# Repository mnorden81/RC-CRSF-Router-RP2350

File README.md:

# RC-CRSF-Router-RP2350 („CRSF-Router 8“)

CRSF-Verteiler für ELRS-Empfänger auf einem **Waveshare RP2350-Zero**. Der große Bruder des [RC-CRSF-Router-ESP32-S3](https://github.com/mnorden81/RC-CRSF-Router-ESP32-S3): gleiche Weiterleitungsregeln, gleiche Bedienung über das Lua-Menü, aber bis zu 7 statt 2 Ports und **kein WLAN**.

Zwei Versionen, ein Sketch (Auswahl oben in `pins.h`):

| Version | Ports | Pins am RP2350-Zero | Im Sender | Platine |
|---|---|---|---|---|
| **Router** | Eingang + 7 Ports | alle, auch die 5 Pads an der Unterkante | `CRSF-Router8@15` | [hardware/Router](hardware/Router/) |
| **Test** | Eingang + 6 Ports | nur die beiden seitlichen Stiftleisten | `CRSF-Router8 Test@15` | keine, nur für das Steckbrett |

> Stand: Firmware **v0.4.1** („Version 2“: Filter, Telemetrie-Bremse, Geräteliste; dazu gezielte Zustellung und Lua-Vorrang nach ELRS-Vorbild), kompiliert und mit Host-Tests geprüft, **noch nicht auf Hardware getestet**. Erster Hardwaretest am 05.11.2026 auf dem Steckbrett (v0.2.0, nur seitliche Stiftleisten): der Sender findet den Router als „CRSF-Router8@14“ neben dem S3-Router und zwei Sound-Minis. Die Router-Platine ist seit 11.11.2026 fertig geroutet (DRC ohne Fehler), aber noch nicht bestellt.

| Testaufbau | RP2350-Zero auf dem Steckbrett |
|---|---|
|  |  |

## Was er macht

Der Router hängt an einem freien CRSF-Port des Empfängers und verteilt CRSF auf bis zu 7 Geräte (Test-Version: 6): Multiswitche (auch die Ziege-One-Module), Soundmodule, Sensoren oder weitere Router.

- Vom Empfänger nach unten geht alles, außer Anfragen an die eigene Adresse. Anfragen an ein Gerät, dessen Port der Router schon kennt, gehen nur an diesen Port (ab v0.4.1).
- Von unten nach oben geht alles (Telemetrie, Lua-Antworten, DEVICE_INFO).
- Zwischen den Ports geht nichts, so entstehen keine Schleifen.
- Weitergegeben werden nur vollständige Frames mit gültiger CRC, unverändert.
- Jeder Port hat eine eigene Warteschlange und sendet nicht blockierend. Ein langsamer Port bremst die anderen nicht aus. Wird es eng, fällt zuerst ein alter RC-Frame weg, dann Telemetrie, Lua-Antworten zuletzt.

### Neu in v0.4.0 („Version 2“)

Die Ideen stammen aus dem Vergleich mit dem CRSF-Switch von Wilhelm Meier (wmucpp). Ohne Änderung im Lua-Menü verhält sich der Router genau wie v0.3.0.

| Funktion | Was sie macht | Wirkt |
|---|---|---|
| **Filter je Port** | RC-Kanäle (0x16/0x17) und LinkStats (0x14/0x1C/0x1D) nach unten je Port an oder aus. Ping, Lua und Schaltbefehle gehen immer durch. | sofort |
| **Telemetrie-Bremse je Port** | Telemetrie von unten nach oben: alle, höchstens 50/20/10/5/2/1 Frames pro Sekunde **je Sensor-Art**, oder aus. Bei RPM, Temperatur und Zellen zählt jede Quelle einzeln. DEVICE_INFO und Lua-Antworten gehen immer hoch. | sofort |
| **Geräteliste** | Der Router fragt 2 s und 6 s nach dem Start alle Ports per Ping ab und merkt sich die Antworten (bis 4 Geräte je Port, auch hinter einem weiteren Router). Lua-Ordner „Geräte“ zeigt sie, „Geräte suchen“ fragt neu ab. Antworten auf den eigenen Ping bleiben im Router. Die USB-Konsole listet jede Änderung. | sofort |

### Neu in v0.4.1 (Ideen aus dem ELRS-Empfänger)

Der ELRS-Empfänger hat seit Version 4.0 selbst einen kleinen CRSF-Router (Funkstrecke, CRSF-Port und auf ESP32-Empfängern ein zweiter UART). Drei seiner Regeln hat der Router übernommen. Im Lua-Menü ändert sich nichts, die Einstellungen bleiben erhalten.

| Funktion | Was sie macht |
|---|---|
| **Adress-Lernen + gezielte Zustellung** | Der Router merkt sich, hinter welchem Port welche Adresse sitzt (aus jedem Lua-, Ping- oder Befehls-Frame von unten und aus Heartbeats 0x0B). Lua-Anfragen und Schaltbefehle an ein bekanntes Gerät gehen nur noch an diesen Port. Unbekannte Ziele, Broadcasts (0x00) und 0xC8 gehen weiter an alle. Steckt man ein Gerät um, gilt der Port, von dem es sich zuletzt gemeldet hat. „Geräte suchen“ vergisst alle gelernten Adressen. |
| **Überschreiben statt Verwerfen** | Wartet noch ein Telemetrie-Frame gleicher Art (bei RPM/Temperatur/Zellen gleicher Quelle) vom selben Port, ersetzt der neue ihn an seinem Platz. So geht immer der neueste Wert hoch, die Schlange läuft nicht voll. |
| **Lua-Vorrang nach oben** | Ping-Antworten und Lua-Frames (0x28–0x2D) überholen wartende Telemetrie. Das Lua-Menü bleibt flüssig, auch wenn viele Module Telemetrie schicken. |

Die USB-Konsole zeigt dazu „gezielt“ und „ersetzt“ in der Statuszeile.

Zum Merken: Schaltet man an einem Port die RC-Kanäle ab, sieht ein Gerät dort (auch ein weiterer Router) kein RC-Signal mehr und geht in Failsafe.

## Status-LED (RGB-LED auf dem Board)

| LED | Bedeutung |
|---|---|
| grün langsam | RC-Signal in Ordnung |
| rot schnell | kein RC-Signal / Failsafe |
| gelb Doppelblitz | Adresskonflikt oder ein Port ließ sich nicht starten |

Sind Rot und Grün vertauscht, im Lua-Menü „LED Farbfolge“ auf **RGB** stellen.

## Lua-Menü (ELRS Lua / TBS Agent)

Ab v0.4.0 werden die Feld-IDs fortlaufend vergeben, sie haben sich gegenüber v0.3.0 verschoben (nur wichtig für eigene Skripte). Die Einstellungen aus v0.3.0 übernimmt der Router beim ersten Start.

| Eintrag | Werte |
|---|---|
| Version | z. B. „0.4.1 Router“ |
| Ordner **Ports (nach Neustart)** | |
| ↳ Port 1 … Port 7 | Aus, 57600, 115200, 400000, **420000**, 921600 |
| Ordner **Filter** → je Port ein Ordner | |
| ↳ RC-Kanaele runter | Aus, **Ein** |
| ↳ LinkStats runter | Aus, **Ein** |
| ↳ Telemetrie hoch | **Alle**, 50/s, 20/s, 10/s, 5/s, 2/s, 1/s, Aus |
| Ordner **Geraete** | |
| ↳ Geraete suchen | Nein, Jetzt |
| ↳ Port 1 … Port 7 | Anzeige, z. B. „Multiswitch@3, Sound@2“, „kein Geraet“, „aus“ |
| Modul Adresse | 0–15, Vorgabe **15** |
| Ordner **Telemetrie** | |
| ↳ Spannung senden | **Aus**, als RxBt, als Zellen |
| ↳ Spannung Korrektur | −0,5 … +0,5 V |
| ↳ Spannung | Anzeige |
| ↳ Temperatur senden | **Aus**, Ein |
| ↳ Chiptemperatur | Anzeige |
| Ordner **Status** | |
| ↳ Frames runter / hoch / Verworfen / Gefiltert / CRC-Fehler unten | Zähler |
| ↳ Adresskonflikt | ja/nein |
| ↳ Ports aktiv | je Port: Nummer = Gerät antwortet, `.` still, `-` aus, `!` Fehler |
| LED Farbfolge | **GRB**, RGB |
| Neustart | Nein, Jetzt |
| Geraetename | „CRSF-Router8“ bzw. „CRSF-Router8 Test“ |

Router: 65 Felder, Test: 59 Felder (Port 7 fehlt überall). Im Sender erscheint der Router als **CRSF-Router8@15** bzw. **CRSF-Router8 Test@15** (Name@Adresse).

## Brauche ich den Router überhaupt? (ELRS 4.x)

Ab ELRS 4.0 haben **ESP32-Empfänger** einen zweiten seriellen Port („Serial 2“, im ELRS-Lua oder WebUI auf „CRSF“ stellen; bei PWM-Empfängern lassen sich dafür PWM-Pins umstellen). Der Empfänger verteilt CRSF dann selbst zwischen beiden Ports.

- **Bis zu 2 Module** an einem ESP32-Empfänger: kein Router nötig.
- **Mehr als 2 Module**, **ESP8285-Empfänger** (nur ein CRSF-Port, z. B. EP1/EP2, RP1–RP3) oder Bedarf an Filtern, Telemetrie-Bremse und Geräteliste: Router verwenden.
- Mit Serial 2 kann der Router auch dort hängen, dann bleibt der erste Port für ein anderes Gerät frei.

## Mehrere Router

Jeder Router hat eine eigene WM-Adresse (0–15 → CRSF 0xC0 + Adresse). Mehrere Router im Modell (auch gemischt mit dem S3-Router) bekommen verschiedene Adressen, z. B. 15, 14, 13. Meldet ein Gerät weiter hinten dieselbe Adresse, blinkt die LED gelb. Router lassen sich verketten; mehr als 3 Router hintereinander sind nicht sinnvoll (je ca. 0,6 ms Verzögerung).

## Anschlüsse (Kurzfassung)

| Port | Router TX | Router RX | Test TX | Test RX | Art |
|---|---|---|---|---|---|
| Uplink (Empfänger) | GP0 | GP1 | GP0 | GP1 | Hardware-UART, fest 420000 Baud |
| Port 1 | GP2 | GP3 | GP2 | GP3 | PIO-UART |
| Port 2 | GP4 | GP5 | GP4 | GP5 | Hardware-UART |
| Port 3 | GP6 | GP7 | GP6 | GP7 | PIO-UART |
| Port 4 | GP8 | GP9 | GP8 | GP14 | PIO-UART |
| Port 5 | GP10 | GP11 | GP15 | GP27 | PIO-UART |
| Port 6 | GP12 | GP13 | GP28 | GP29 | PIO-UART |
| Port 7 | GP14 | GP15 | – | – | PIO-UART |
| Spannung | GP26 | | GP26 | | nur mit externem Teiler 33k/10k, auf der Platine nicht vorhanden |

Lage am Board (Oberseite, USB oben): rechte Leiste GP0–GP8, untere Kante GP9–GP13 (nur Lötpads), linke Leiste 5V, GND, 3V3, GP29, GP28, GP27, GP26, GP15, GP14. Die **Router**-Version braucht die Pads unten (5er-Stiftleiste einlöten), die **Test**-Version kommt mit den beiden seitlichen Leisten aus. Mehr als 8 UARTs (2 Hardware + 6 PIO) schafft der RP2350 nicht, deshalb sind 7 Ports das Maximum.

TX des Routers an RX des Geräts und umgekehrt, GND gemeinsam. Details und Schaltplan: [hardware/README.md](hardware/README.md).

## Firmware flashen

Der RP2350 hat kein WLAN, Updates gehen immer über USB. Am einfachsten ist Weg 1, dafür braucht man keine Software.

### Weg 1: Fertige Datei aus GitHub (ohne Arduino IDE)

1. Auf GitHub angemeldet sein (sonst gibt es keinen Download-Knopf).
2. In diesem Repo oben auf **Actions** klicken, links den Workflow **Firmware bauen** wählen.
3. Den obersten Lauf mit grünem Haken öffnen (Branch `main`).
4. Ganz unten unter **Artifacts** **crsf-router8-rp2350-Router** herunterladen (für das Steckbrett: **crsf-router8-rp2350-Test**) und die ZIP-Datei entpacken. Darin liegt `CRSF-Router8_Router.uf2` bzw. `CRSF-Router8_Test.uf2`.
   Steht dort nichts (Artefakte werden nach 90 Tagen gelöscht): rechts oben **Run workflow** → **Run workflow** klicken, nach ca. 3 Minuten ist ein neuer Lauf fertig.
5. Am RP2350-Zero die Taste **BOOT** gedrückt halten und dabei das USB-C-**Datenkabel** einstecken, dann loslassen.
6. Am PC erscheint ein neues Laufwerk **RP2350** (wie ein USB-Stick).
7. Die `.uf2`-Datei mit der Maus auf dieses Laufwerk ziehen. Das Laufwerk verschwindet, der Router startet von selbst neu. Fertig.

### Weg 2: Arduino IDE

**Einmalig einrichten**

1. Arduino IDE 2.x installieren (https://www.arduino.cc/en/software).
2. **Datei → Einstellungen → Zusätzliche Boardverwalter-URLs**:
   `https://github.com/earlephilhower/arduino-pico/releases/download/global/package_rp2040_index.json`
3. **Werkzeuge → Board → Boardverwalter**: „pico“ suchen, **Raspberry Pi Pico/RP2040/RP2350** (von Earle F. Philhower) in Version **6.3.2** installieren.
4. Weitere Bibliotheken sind nicht nötig.

**Flashen**

1. Repo herunterladen: oben auf GitHub **Code → Download ZIP**, entpacken (oder den vorhandenen Ordner nehmen).
2. **Datei → Öffnen** und `firmware/RC_CRSF_Router_RP2350/RC_CRSF_Router_RP2350.ino` wählen.
3. Version wählen: oben in `pins.h` steht `#define VARIANTE_ROUTER` (Vorgabe, für die Platine). Für die Test-Version (Steckbrett) diese Zeile mit `//` auskommentieren und bei `//#define VARIANTE_TEST` die `//` entfernen.
4. **Werkzeuge → Board → Raspberry Pi Pico/RP2040/RP2350 → Waveshare RP2350 Zero** wählen. Die übrigen Einstellungen unter Werkzeuge bleiben auf Standard.
5. Beim **allerersten Mal**: BOOT-Taste gedrückt halten, USB einstecken, loslassen. Unter **Werkzeuge → Port** „UF2 Board“ wählen.
   Ab dem zweiten Mal: einfach einstecken und unter **Werkzeuge → Port** den COM-Port wählen.
6. Auf den Pfeil **Hochladen** klicken. Der Router startet danach von selbst neu.

**Wenn das Hochladen nicht klappt** (kein Port oder „No drive to deploy“): USB abziehen, BOOT gedrückt halten, wieder einstecken und mit Port „UF2 Board“ erneut hochladen.

Der serielle Monitor (115200) zeigt alle 10 s eine Statuszeile.

## Aufbau des Repos

| Ordner | Inhalt |
|---|---|
| `firmware/RC_CRSF_Router_RP2350/` | Arduino-Sketch (siehe [firmware/README.md](firmware/README.md)) |
| `tests/` | Host-Tests des Routers (`sh tests/run_tests.sh`) |
| `hardware/Router/` | KiCad-Projekt der Router-Platine (geroutet, DRC ohne Fehler), nur THT-Bauteile, plus 3D-Modell `hardware/3d-modell.html` (siehe [hardware/README.md](hardware/README.md)) |
| `hardware/gehaeuse/` | 3D-Druck-Gehäuse (STL/STEP, CadQuery-Quelle, 3D-Vorschau), siehe [hardware/gehaeuse/README.md](hardware/gehaeuse/README.md) |
| `docs/` | Projektbeschreibung (DOCX), Fotos unter `docs/bilder/` |

## Herkunft

Die CRSF-Bibliothek stammt aus RC_Common (CRSF_ESP32 1.1.0), Basis ist [CRSF_ESP32 von Ziege-One](https://github.com/Ziege-One/CRSF_ESP32) (GPL-3.0).

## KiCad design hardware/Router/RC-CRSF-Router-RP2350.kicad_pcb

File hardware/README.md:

# Hardware CRSF-Router 8

Basis ist ein **Waveshare RP2350-Zero** (ca. 23,5 × 18 mm, USB-C, RGB-LED an GP16, BOOT- und RESET-Taste), gesteckt auf eine Verteilerplatine. Jeder Teilnehmer bekommt ein 4-poliges Kabel mit GND, +V und den beiden Signalen, wie bei einem Servoverteiler.

Es gibt **eine** Platine für den Router (Ordner [`Router/`](Router/)): Eingang + 7 Ports, alle Bauteile bedrahtet (THT), 38,4 × 25,5 mm, 2 Lagen. Sie nutzt alle Pins am RP2350-Zero, also beide seitlichen Leisten **und** die 5 Pads unten (GP9–GP13). Firmware-Version `VARIANTE_ROUTER` in `firmware/RC_CRSF_Router_RP2350/pins.h` (Vorgabe).

Die Firmware-Version **Test** (`VARIANTE_TEST`, Eingang + 6 Ports, nur die seitlichen Leisten) ist nur für den Aufbau auf dem Steckbrett gedacht. Für sie gibt es keine Platine.

> Stand 11.11.2026 (abends): **Platine fertig geroutet** (von Martin in KiCad 9, beide Lagen: 144 Leiterbahn-Stücke, 6 Vias, keine Kupferflächen). DRC: 0 Fehler, 0 offene Verbindungen. ERC: 0 Fehler, nur 19 Warnungen „Symbol stimmt nicht mit Bibliothek überein“ bei den Power-Symbolen (harmlos, verschwindet mit „Symbole aus Bibliothek aktualisieren“). Vor der Bestellung noch prüfen: Footprint des RP2350-Zero am echten Board, Abmessungen von F1 im Datenblatt, und die Beschriftung auf der Unterseite (sie liegt teilweise auf Pads, der Hersteller schneidet sie dort weg). Mehr als 8 UARTs schafft der RP2350 nicht (2 Hardware-UARTs + 6 PIO-UARTs), deshalb sind 7 Ports das Maximum.

| Oberseite | Unterseite |
|---|---|
|  |  |

Leiterbahnen beider Lagen (rot oben, blau unten):

3D-Modell (vereinfachte Bauteilkörper, Maße aus der Platine): [`3d-modell.html`](3d-modell.html) herunterladen und im Browser öffnen (braucht Internet für die 3D-Bibliothek).

**Gehäuse für den 3D-Druck:** Unterteil und Deckel zum Aufklipsen, Steckerfeld oben und rechts offen, siehe [`gehaeuse/`](gehaeuse/).

## Aufbau so kompakt wie möglich (11.11.2026)

- Platine 38,4 × 25,5 mm: links der RP2350-Zero (USB-C ragt etwas über die Kante), darunter in einer Reihe parallel zum Zero C1, D1 (liegend) und F1, rechts die Steckerleiste.
- Keine Befestigungslöcher. Befestigung z. B. mit doppelseitigem Klebeband oder Schrumpfschlauch.
- Beschriftung (Name, T/R/V/G-Erklärung, Hinweis „kein HV-BEC“) auf der Unterseite. Oben nur T R V G und die Reihen U, 1–7.
- Steckerleiste in der Reihenfolge **T R V G** (Signale zum RP2350 hin, GND außen), damit TX/RX auf kurzem Weg zum Zero laufen. Signale 0,2 mm, Abstand 0,2 mm: zwischen zwei Pads der Leiste passt eine Leiterbahn.

## Versorgung

- **Nur vom Empfänger:** Die 5–6 V kommen über die Reihe U (Pin V) vom Empfänger-BEC. Es gibt keinen eigenen BEC-Eingang. **Kein HV-BEC (7,4/8,4 V) am Empfänger!**
- **Kein Spannungsregler:** Der RP2350-Zero bekommt VBUS über D1 (1N5819, ca. 0,3 V Verlust) an seinen 5-V-Pin. D1 verhindert, dass USB den Empfänger und die Ports speist.
- **Eine gemeinsame Sicherung** F1 (PTC 3 A) für alle Ports. Bei einem Kurzschluss an einem Port läuft der Empfänger weiter. Nach Beseitigung des Fehlers schaltet sie selbst wieder ein.
- C1 (100 µF) puffert kurze Stromspitzen der Module. Ohne ihn läuft der Router auch.
- Hat ein Modul eine eigene Versorgung, bekommt es einfach kein V-Kabel, damit zwei Netzteile nicht gegeneinander arbeiten.
- Große Verbraucher (Lasten der Multiswitche, Lautsprecher-Verstärker) nicht über diese Platine versorgen.
- **Keine Spannungsmessung:** GP26 bleibt frei, in Lua „Spannung senden“ aus lassen.

## Stückliste

| Ref | Anzahl | Wert | Bauform | Hinweis |
|---|---|---|---|---|
| U1 | 1 | Waveshare RP2350-Zero | direkt aufgelötet | Randkontakte auf die Pads gelötet, ohne Buchsenleisten |
| D1 | 1 | 1N5819 | DO-41, liegend (RM 7,62) | VBUS zum 5-V-Pin, kein Rückstrom bei USB |
| F1 | 1 | PTC 3 A / 16 V, Bourns MF-RG300 | radial, stehend | gemeinsame Sicherung aller Ports |
| C1 | 1 | 100 µF / 10 V | Elko radial Ø 5 mm, RM 2 | puffert Stromspitzen, kann zur Not entfallen |
| J1–J8 | 8 | Stiftleiste 1×4 | 2,54 mm, gerade | Uplink + Port 1–7 |

## KiCad-Projekte

Der Ordner `Router/` enthält ein vollständiges Projekt:

| Datei | Inhalt |
|---|---|
| `RC-CRSF-Router-RP2350.kicad_pro/.kicad_sch/.kicad_pcb` | Projekt, Schaltplan, Platine |
| `RC-CRSF-Router-RP2350_Schaltplan.pdf` | Schaltplan als PDF |
| `Router8.kicad_sym`, `footprints.pretty/` | Projektbibliothek: Symbol und Footprint RP2350-Zero, Stiftleiste 1×4 für die Schiene |
| `sym-lib-table`, `fp-lib-table` | binden die Projektbibliothek ein |
| `vorschau-platine.png`, `vorschau-unterseite.png` | 3D-Ansicht der gerouteten Platine von oben und unten (KiCad-Rendering) |
| `vorschau-routing.png` | Leiterbahnen beider Lagen |

Gespeichert mit KiCad 9.0. Leiterbahnen für TX/RX 0,2 mm (bei 420 kBaud und wenigen mA völlig ausreichend), Netzklasse **Power** (GND, VBUS, +5V, +V der Ports) 0,5 mm mit Via 0,9/0,5 mm, sonst Via 0,6/0,3 mm, Abstand überall 0,2 mm. Das kann jeder übliche Platinenhersteller.

**Nächster Schritt:** Gerber- und Bohrdaten für den Hersteller exportieren (KiCad: Datei → Fertigungsdateien). Sie liegen noch nicht im Repo.

**RP2350-Zero direkt aufgelötet:** Das Board liegt flach auf der Platine, seine Randkontakte werden auf die Pads gelötet (alternativ kurze Stiftleisten durch beide Platinen). Dabei auch die 5 Pads an der Unterkante (GP9–GP13) verlöten. Vor dem Auflöten die Firmware einmal per USB aufspielen und testen.

## Steckerleiste (2,54 mm, gerade)

| Reihe | Bedeutung |
|---|---|
| U (J1) | Uplink zum Empfänger, von hier kommt die Versorgung |
| 1–7 (J2–J8) | Port 1–7, +V über die Sicherung F1 |

Spalten von links: **T** = Router empfängt, vom TX des Geräts, **R** = Router sendet, an RX des Geräts, **V** = +5–6 V, **G** = GND (eckiges Pad, rechts außen). Damit wird jedes Kabel gerade gesteckt.

## Pinbelegung RP2350-Zero

Die Spalten „Test“ gelten nur für den Steckbrett-Aufbau ohne Platine.

| Port | Router TX | Router RX | Test TX | Test RX |
|---|---|---|---|---|
| Uplink (Hardware-UART0) | GP0 | GP1 | GP0 | GP1 |
| Port 1 (PIO) | GP2 | GP3 | GP2 | GP3 |
| Port 2 (Hardware-UART1) | GP4 | GP5 | GP4 | GP5 |
| Port 3 (PIO) | GP6 | GP7 | GP6 | GP7 |
| Port 4 (PIO) | GP8 | GP9 | GP8 | GP14 |
| Port 5 (PIO) | GP10 | GP11 | GP15 | GP27 |
| Port 6 (PIO) | GP12 | GP13 | GP28 | GP29 |
| Port 7 (PIO) | GP14 | GP15 | – | – |
| frei | GP26–GP29 | | GP26, GP9–GP13 (Pads) | |

Lage am Board (Oberseite, USB oben): rechte Leiste GP0–GP8, untere Kante GP9–GP13 (nur Pads), linke Leiste 5V, GND, 3V3, GP29, GP28, GP27, GP26, GP15, GP14.

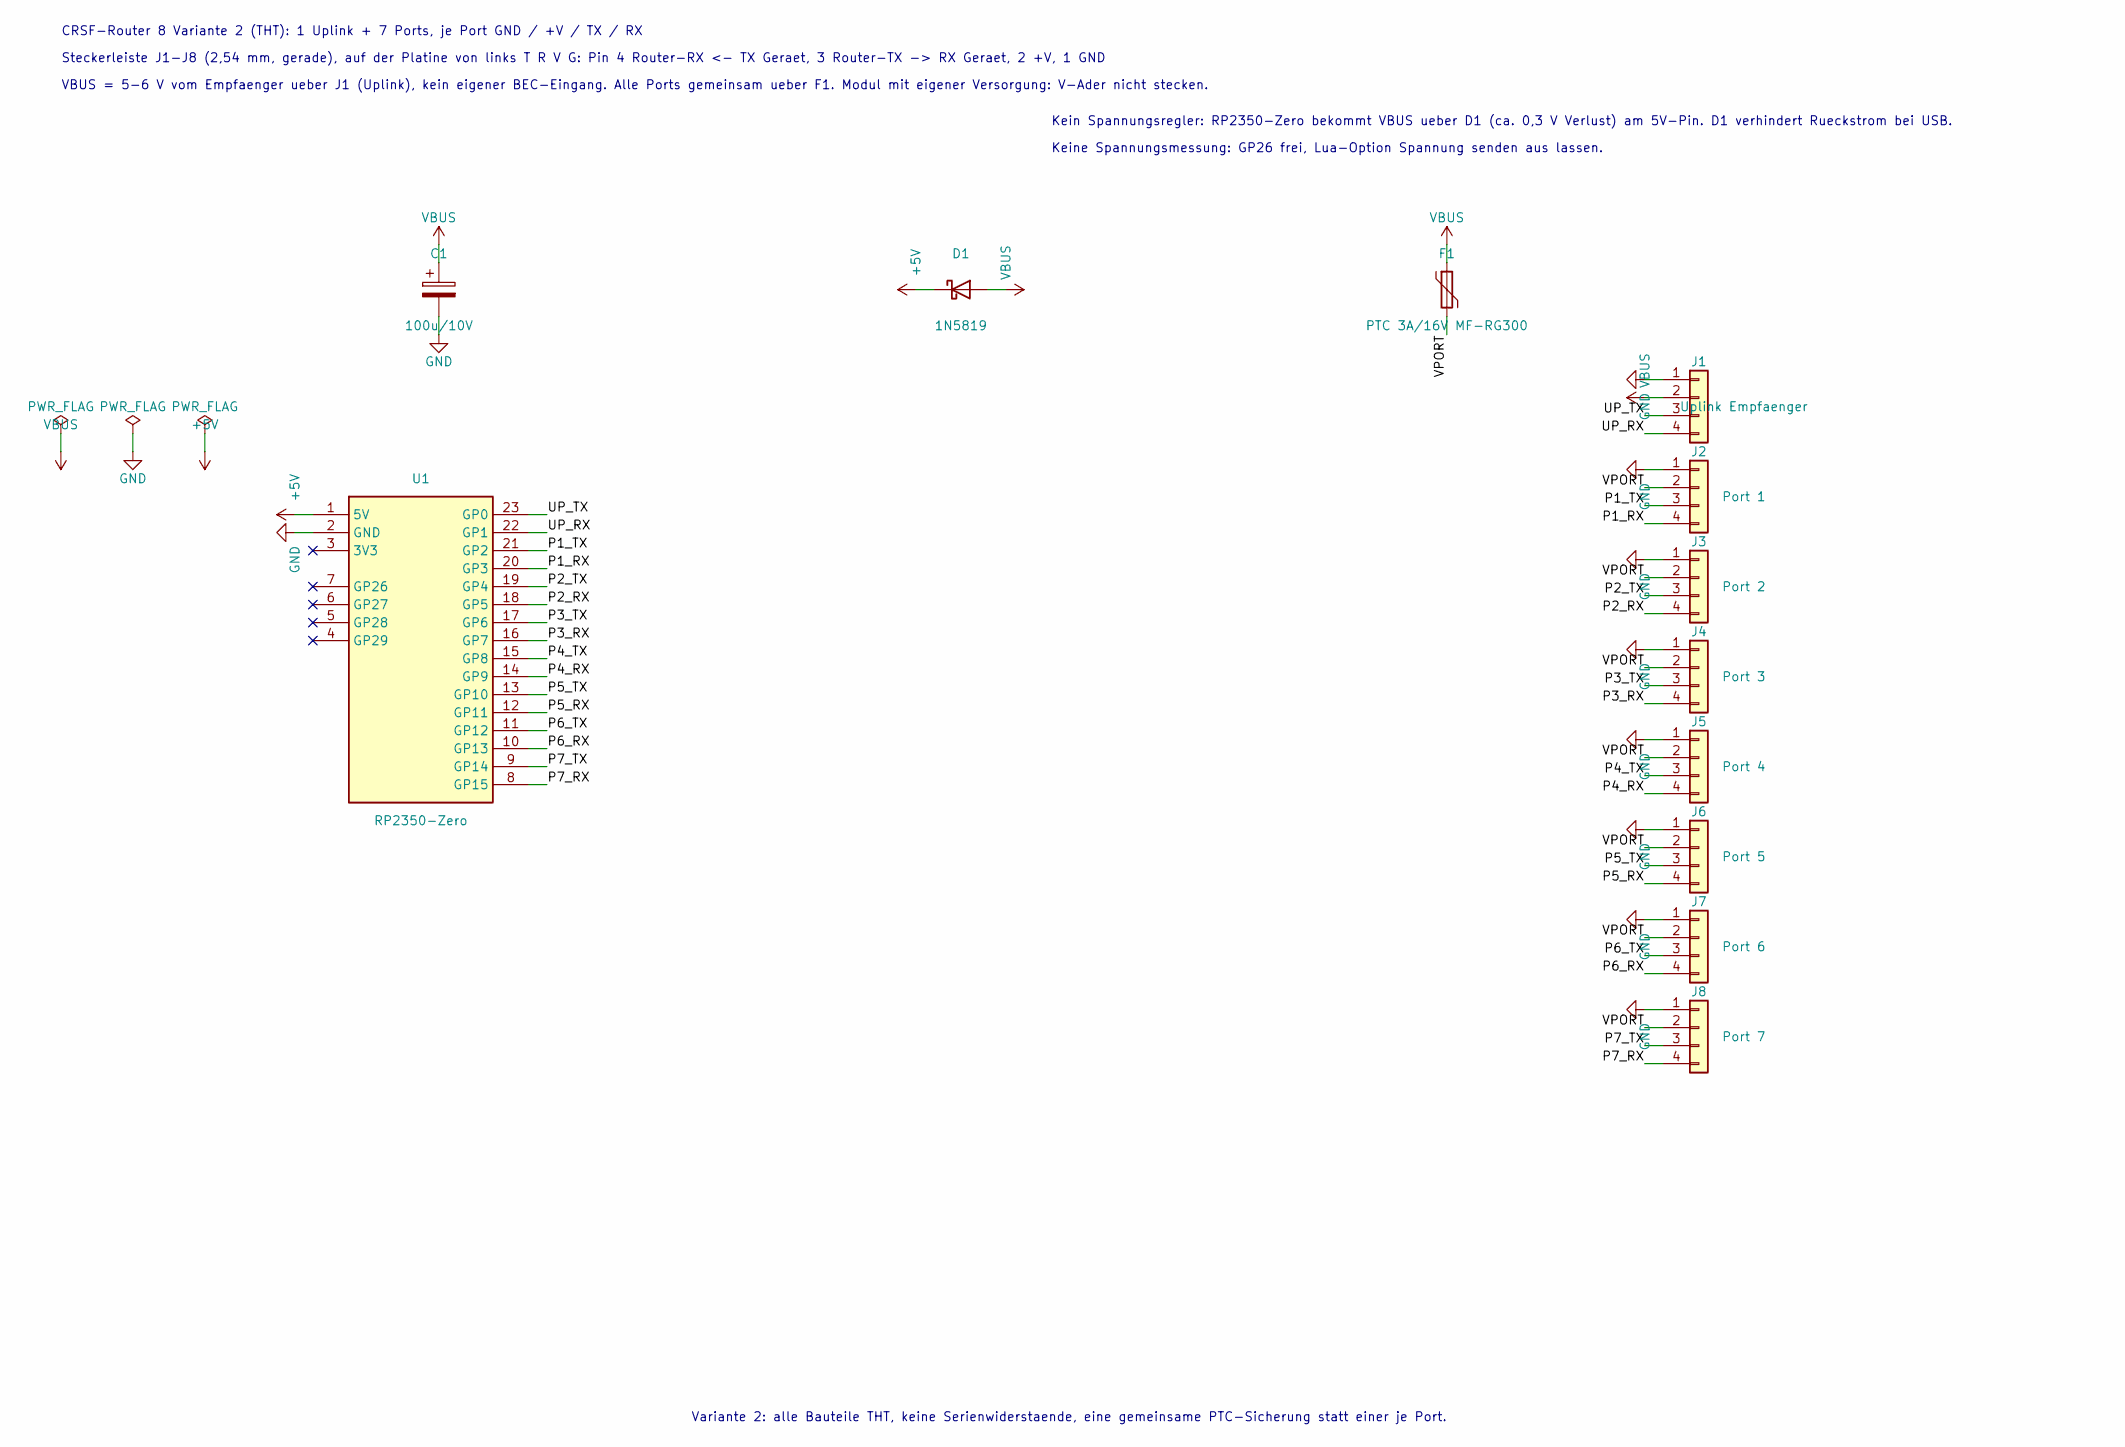
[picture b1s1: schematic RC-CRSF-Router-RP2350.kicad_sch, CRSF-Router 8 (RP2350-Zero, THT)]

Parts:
C1: 100u/10V; CP_Radial_D5.0mm_P2.00mm
D1: 1N5819; D_DO-41_SOD81_P7.62mm_Horizontal
F1: PTC 3A/16V MF-RG300; Fuse_Bourns_MF-RG300
J1: Uplink Empfaenger; PinHeader_1x04_Rail
J2: Port 1; PinHeader_1x04_Rail
J3: Port 2; PinHeader_1x04_Rail
J4: Port 3; PinHeader_1x04_Rail
J5: Port 4; PinHeader_1x04_Rail
J6: Port 5; PinHeader_1x04_Rail
J7: Port 6; PinHeader_1x04_Rail
J8: Port 7; PinHeader_1x04_Rail
U1: RP2350-Zero; RP2350-Zero_Socket

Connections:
+5V: D1.1 (K), U1.1 (5V)
/P1_RX: J2.4, U1.20 (GP3)
/P1_TX: J2.3, U1.21 (GP2)
/P2_RX: J3.4, U1.18 (GP5)
/P2_TX: J3.3, U1.19 (GP4)
/P3_RX: J4.4, U1.16 (GP7)
/P3_TX: J4.3, U1.17 (GP6)
/P4_RX: J5.4, U1.14 (GP9)
/P4_TX: J5.3, U1.15 (GP8)
/P5_RX: J6.4, U1.12 (GP11)
/P5_TX: J6.3, U1.13 (GP10)
/P6_RX: J7.4, U1.10 (GP13)
/P6_TX: J7.3, U1.11 (GP12)
/P7_RX: J8.4, U1.8 (GP15)
/P7_TX: J8.3, U1.9 (GP14)
/UP_RX: J1.4, U1.22 (GP1)
/UP_TX: J1.3, U1.23 (GP0)
/VPORT: F1.2, J2.2, J3.2, J4.2, J5.2, J6.2, J7.2, J8.2
GND: C1.2, J1.1, J2.1, J3.1, J4.1, J5.1, J6.1, J7.1, J8.1, U1.2 (GND)
VBUS: C1.1, D1.2 (A), F1.1, J1.2

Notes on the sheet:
Steckerleiste J1-J8 (2,54 mm, gerade), auf der Platine von links T R V G: Pin 4 Router-RX <- TX Geraet, 3 Router-TX -> RX Geraet, 2 +V, 1 GND
CRSF-Router 8 Variante 2 (THT): 1 Uplink + 7 Ports, je Port GND / +V / TX / RX
Variante 2: alle Bauteile THT, keine Serienwiderstaende, eine gemeinsame PTC-Sicherung statt einer je Port.
VBUS = 5-6 V vom Empfaenger ueber J1 (Uplink), kein eigener BEC-Eingang. Alle Ports gemeinsam ueber F1. Modul mit eigener Versorgung: V-Ader nicht stecken.
Kein Spannungsregler: RP2350-Zero bekommt VBUS ueber D1 (ca. 0,3 V Verlust) am 5V-Pin. D1 verhindert Rueckstrom bei USB.
Keine Spannungsmessung: GP26 frei, Lua-Option Spannung senden aus lassen.

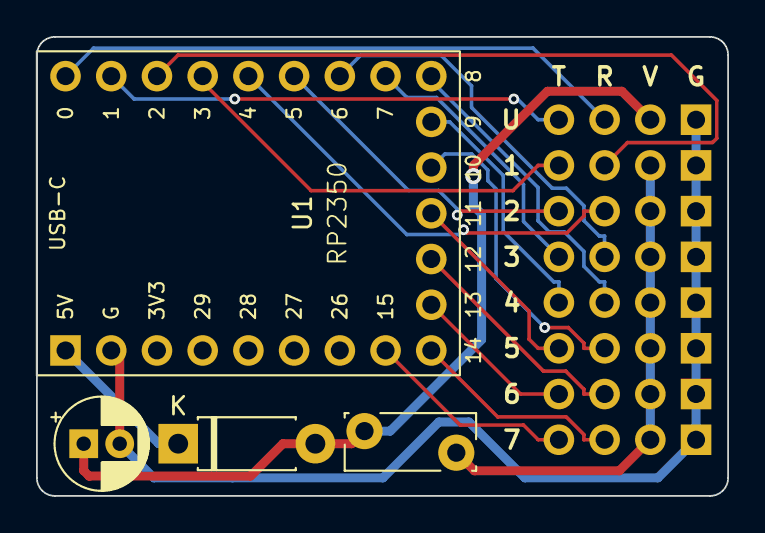
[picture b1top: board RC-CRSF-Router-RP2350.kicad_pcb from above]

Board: 2 copper layers, 38.4 x 25.5 mm, 12 parts (0 on the bottom side), 20 nets.

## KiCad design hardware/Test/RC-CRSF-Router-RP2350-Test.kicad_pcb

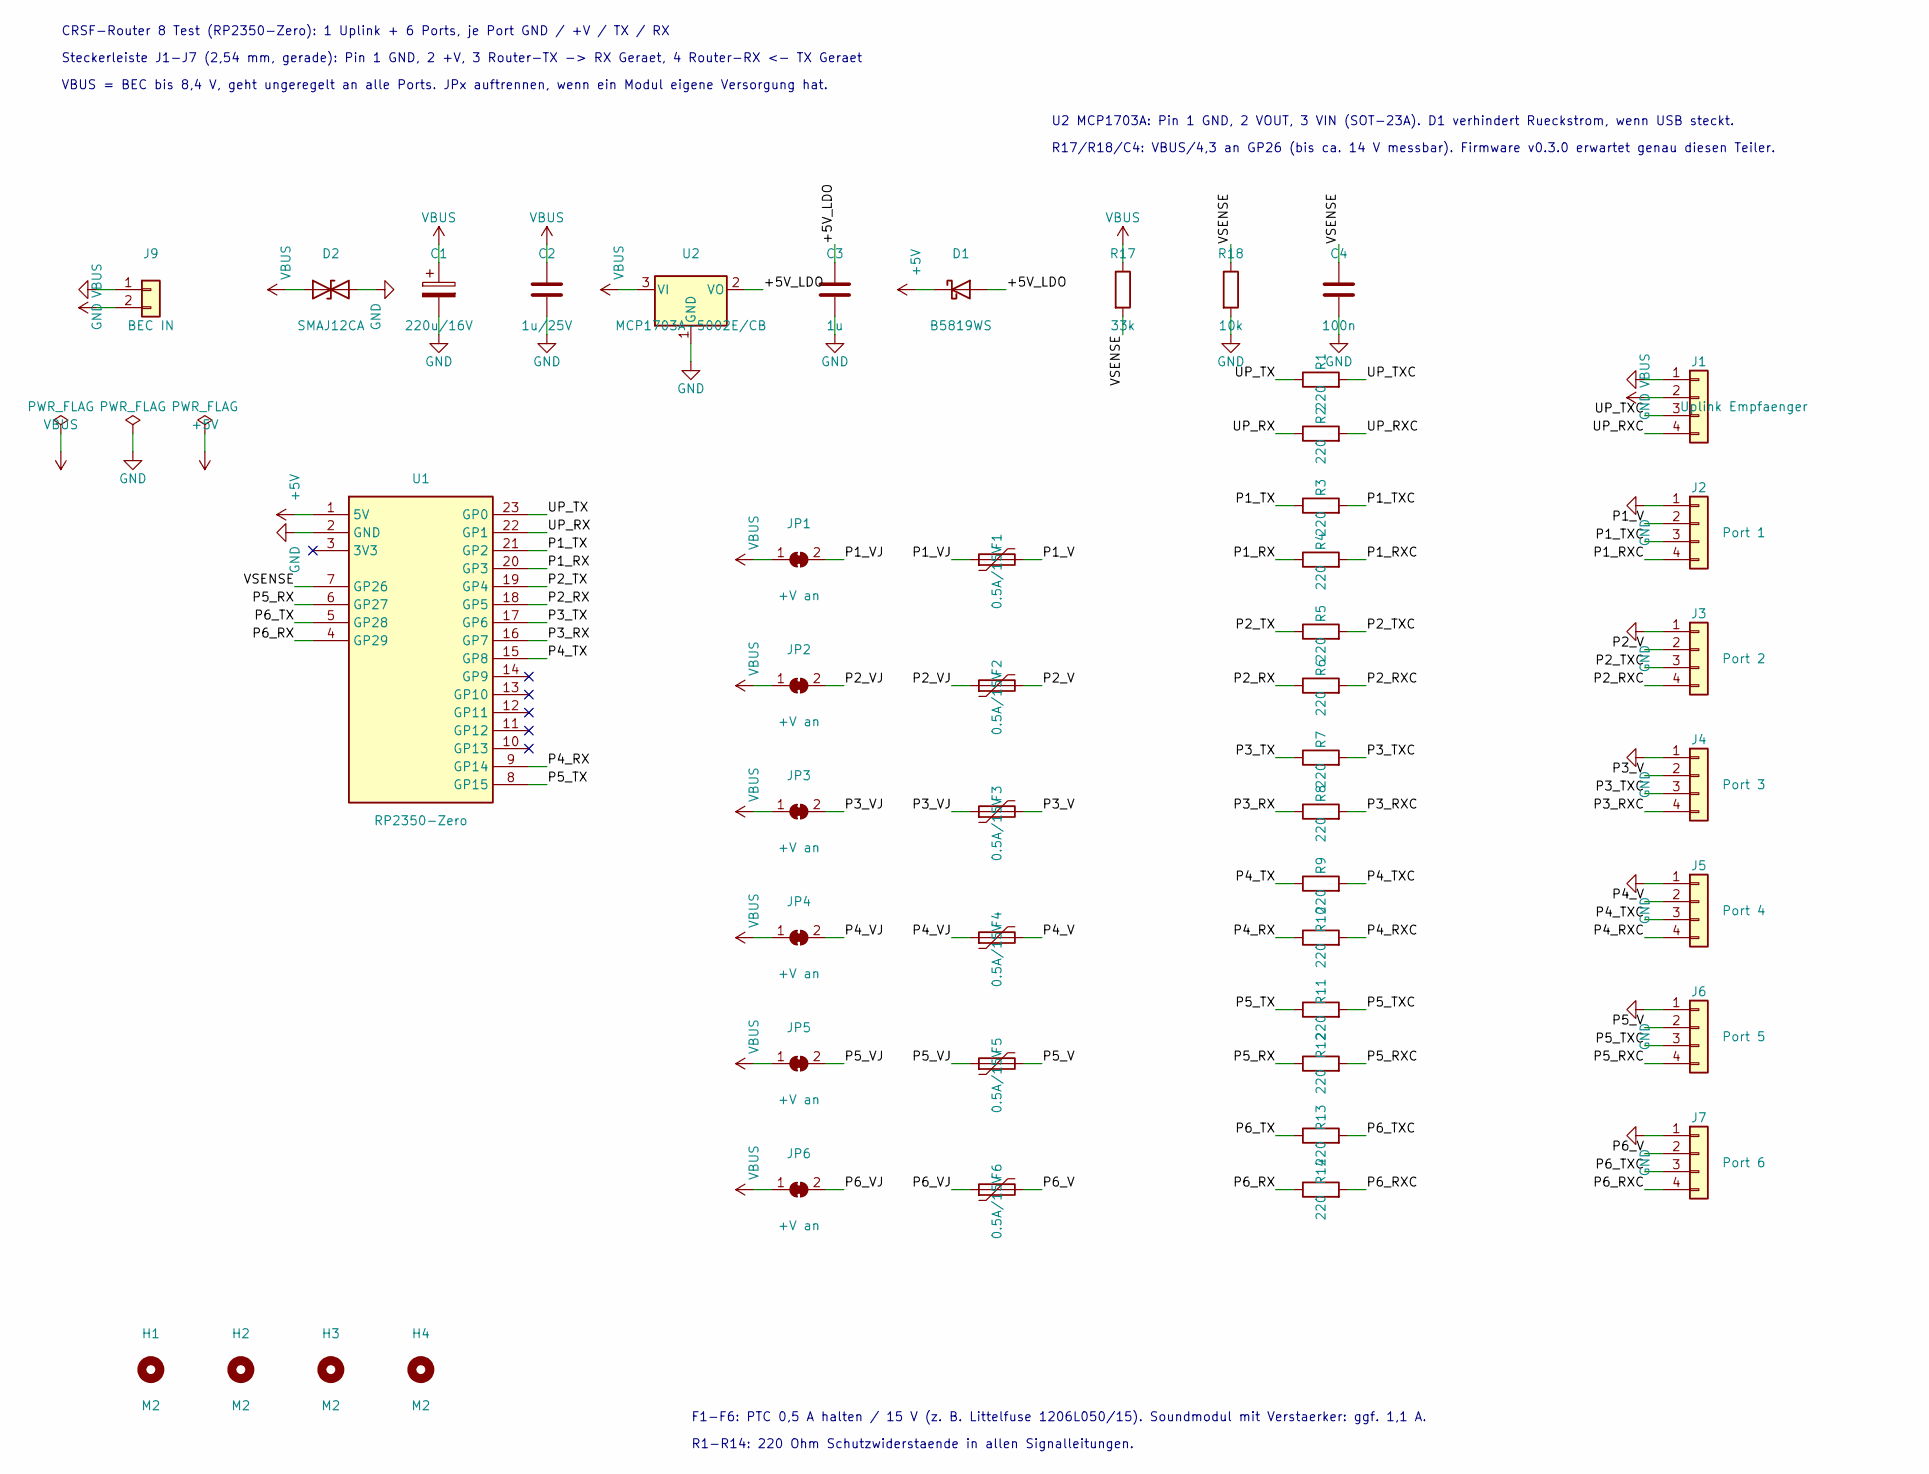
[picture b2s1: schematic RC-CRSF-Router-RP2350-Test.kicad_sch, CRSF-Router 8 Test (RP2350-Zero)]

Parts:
C1: 220u/16V; CP_Elec_6.3x7.7
C2: 1u/25V; C_0805_2012Metric
C3: 1u; C_0805_2012Metric
C4: 100n; C_0805_2012Metric
D1: B5819WS; D_SOD-323
D2: SMAJ12CA; D_SMA
F1, F2, F3, F4, F5, F6: 0.5A/15V; Fuse_1206_3216Metric
H1, H2, H3, H4: M2; MountingHole_2.2mm_M2
J1: Uplink Empfaenger; PinHeader_1x04_Rail
J2: Port 1; PinHeader_1x04_Rail
J3: Port 2; PinHeader_1x04_Rail
J4: Port 3; PinHeader_1x04_Rail
J5: Port 4; PinHeader_1x04_Rail
J6: Port 5; PinHeader_1x04_Rail
J7: Port 6; PinHeader_1x04_Rail
J9: BEC IN; PinHeader_1x02_P2.54mm_Vertical
JP1, JP2, JP3, JP4, JP5, JP6: +V an; SolderJumper-2_P1.3mm_Bridged_RoundedPad1.0x1.5mm
R1, R2, R3, R4, R5, R6, R7, R8, R9, R10, R11, R12, R13, R14: 220; R_0805_2012Metric
R17: 33k; R_0805_2012Metric
R18: 10k; R_0805_2012Metric
U1: RP2350-Zero; RP2350-Zero_Socket
U2: MCP1703A-5002E/CB; SOT-23

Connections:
+5V: D1.1 (K), U1.1 (5V)
/+5V_LDO: C3.1, D1.2 (A), U2.2 (VO)
/P1_RX: R4.1, U1.20 (GP3)
/P1_RXC: J2.4, R4.2
/P1_TX: R3.1, U1.21 (GP2)
/P1_TXC: J2.3, R3.2
/P1_V: F1.2, J2.2
/P1_VJ: F1.1, JP1.2 (B)
/P2_RX: R6.1, U1.18 (GP5)
/P2_RXC: J3.4, R6.2
/P2_TX: R5.1, U1.19 (GP4)
/P2_TXC: J3.3, R5.2
/P2_V: F2.2, J3.2
/P2_VJ: F2.1, JP2.2 (B)
/P3_RX: R8.1, U1.16 (GP7)
/P3_RXC: J4.4, R8.2
/P3_TX: R7.1, U1.17 (GP6)
/P3_TXC: J4.3, R7.2
/P3_V: F3.2, J4.2
/P3_VJ: F3.1, JP3.2 (B)
/P4_RX: R10.1, U1.9 (GP14)
/P4_RXC: J5.4, R10.2
/P4_TX: R9.1, U1.15 (GP8)
/P4_TXC: J5.3, R9.2
/P4_V: F4.2, J5.2
/P4_VJ: F4.1, JP4.2 (B)
/P5_RX: R12.1, U1.6 (GP27)
/P5_RXC: J6.4, R12.2
/P5_TX: R11.1, U1.8 (GP15)
/P5_TXC: J6.3, R11.2
/P5_V: F5.2, J6.2
/P5_VJ: F5.1, JP5.2 (B)
/P6_RX: R14.1, U1.4 (GP29)
/P6_RXC: J7.4, R14.2
/P6_TX: R13.1, U1.5 (GP28)
/P6_TXC: J7.3, R13.2
/P6_V: F6.2, J7.2
/P6_VJ: F6.1, JP6.2 (B)
/UP_RX: R2.1, U1.22 (GP1)
/UP_RXC: J1.4, R2.2
/UP_TX: R1.1, U1.23 (GP0)
/UP_TXC: J1.3, R1.2
/VSENSE: C4.1, R17.2, R18.1, U1.7 (GP26)
GND: C1.2, C2.2, C3.2, C4.2, D2.2 (A2), J1.1, J2.1, J3.1, J4.1, J5.1, J6.1, J7.1, J9.1, R18.2, U1.2 (GND), U2.1 (GND)
VBUS: C1.1, C2.1, D2.1 (A1), J1.2, J9.2, JP1.1 (A), JP2.1 (A), JP3.1 (A), JP4.1 (A), JP5.1 (A), JP6.1 (A), R17.1, U2.3 (VI)

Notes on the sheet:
CRSF-Router 8 Test (RP2350-Zero): 1 Uplink + 6 Ports, je Port GND / +V / TX / RX
Steckerleiste J1-J7 (2,54 mm, gerade): Pin 1 GND, 2 +V, 3 Router-TX -> RX Geraet, 4 Router-RX <- TX Geraet
VBUS = BEC bis 8,4 V, geht ungeregelt an alle Ports. JPx auftrennen, wenn ein Modul eigene Versorgung hat.
U2 MCP1703A: Pin 1 GND, 2 VOUT, 3 VIN (SOT-23A). D1 verhindert Rueckstrom, wenn USB steckt.
R17/R18/C4: VBUS/4,3 an GP26 (bis ca. 14 V messbar). Firmware v0.3.0 erwartet genau diesen Teiler.
F1-F6: PTC 0,5 A halten / 15 V (z. B. Littelfuse 1206L050/15). Soundmodul mit Verstaerker: ggf. 1,1 A.
R1-R14: 220 Ohm Schutzwiderstaende in allen Signalleitungen.

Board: 2 copper layers, 48 parts (0 on the bottom side), 45 nets, no tracks yet.

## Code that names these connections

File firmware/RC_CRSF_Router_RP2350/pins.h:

#ifndef PINS_H
#define PINS_H

/*
 * pins.h  -  CRSF-Router 8 (Waveshare RP2350-Zero)
 *
 * Zwei Varianten, gleicher Sketch. Genau EINE Zeile unten aktiv lassen:
 *
 *   VARIANTE_ROUTER  "Router": Eingang + 7 Ports, alle Pins (GP0-GP15).
 *                    Braucht auch die Loetpads an der unteren Kante
 *                    (GP9-GP13): dort eine 5er-Stiftleiste einloeten.
 *                    Platine: hardware/Router/
 *   VARIANTE_TEST    "Test": Eingang + 6 Ports, nur die beiden seitlichen
 *                    Stiftleisten, Pads GP9-GP13 bleiben frei. Gut fuer
 *                    Steckbrett und Probeaufbau. Platine: hardware/Test/
 *
 * Belegung RP2350-Zero (Oberseite, USB oben):
 *   rechte Leiste:  GP0 GP1 GP2 GP3 GP4 GP5 GP6 GP7 GP8
 *   untere Kante:   GP9 GP10 GP11 GP12 GP13 (nur Loetpads)
 *   linke Leiste:   5V GND 3V3 GP29 GP28 GP27 GP26 GP15 GP14
 * Mehr als 8 UARTs gehen nicht: 2 Hardware-UARTs + 6 PIO-UARTs
 * (je 2 der 12 PIO-State-Machines).
 * GPIO16 ist die RGB-LED (WS2812, auf dem Board), GPIO26 misst die Spannung.
 * Alle Pins vertragen nur 3,3 V. CRSF-Empfaenger und -Module arbeiten mit
 * 3,3-V-Pegeln, das passt direkt.
 */

#if !defined(VARIANTE_ROUTER) && !defined(VARIANTE_TEST)
#define VARIANTE_ROUTER      // Vollversion: Eingang + 7 Ports
//#define VARIANTE_TEST      // Testversion: Eingang + 6 Ports, nur seitliche Leisten
#endif
#if defined(VARIANTE_ROUTER) && defined(VARIANTE_TEST)
#error "Nur eine Variante waehlen: VARIANTE_ROUTER oder VARIANTE_TEST"
#endif

// ── Uplink zum Empfaenger: Hardware-UART0 (Serial1), fest 420000 Baud ─
#define PIN_UPLINK_TX  0
#define PIN_UPLINK_RX  1

// ── Port 2: Hardware-UART1 (Serial2) ─────────────────────────────────
#define PIN_P2_TX      4
#define PIN_P2_RX      5

// ── Port 1 und 3-7: PIO-UARTs (SerialPIO, beliebige Pins) ───────────
#define PIN_P1_TX      2
#define PIN_P1_RX      3
#define PIN_P3_TX      6
#define PIN_P3_RX      7

#if defined(VARIANTE_ROUTER)
#define VARIANTE_NAME  "Router"
#define PORT_COUNT     7
#define PIN_P4_TX      8
#define PIN_P4_RX      9
#define PIN_P5_TX      10
#define PIN_P5_RX      11
#define PIN_P6_TX      12
#define PIN_P6_RX      13
#define PIN_P7_TX      14
#define PIN_P7_RX      15
// GP27, GP28, GP29: frei (Reserve)
#else
#define VARIANTE_NAME  "Test"
#define PORT_COUNT     6
// Port 4: TX rechts unten (GP8), RX links unten (GP14)
#define PIN_P4_TX      8
#define PIN_P4_RX      14
// Port 5: GP15 und GP27 (dazwischen GP26 = Spannung)
#define PIN_P5_TX      15
#define PIN_P5_RX      27
#define PIN_P6_TX      28
#define PIN_P6_RX      29
#endif

// ── Status-LED: RGB-LED (WS2812) des RP2350-Zero ─────────────────────
// Die PIO-Einheiten gehoeren den UARTs, die LED wird deshalb per
// Software angesteuert (ca. 30 us je Farbwechsel).
#define PIN_STATUS_LED 16

// ── Spannung: Spannungsteiler an ADC0 ────────────────────────────────
//   +V (BEC/Empfaenger) ── 33 kOhm ──┬── GPIO26
//                                    └── 10 kOhm ── GND
// Teiler 4,3 : 1 -> bis ca. 14 V messbar. Ohne Teiler "Spannung senden"
// auf Aus lassen (offener Pin liefert Zufallswerte).
#define PIN_VSENSE       26
#define VSENSE_R_TOP     33.0f
#define VSENSE_R_BOTTOM  10.0f

#endif // PINS_H
